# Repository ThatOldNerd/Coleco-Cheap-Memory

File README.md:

# Coleco-Cheap-Memory
This is an inexpensive memory module for the Colecovision Adam

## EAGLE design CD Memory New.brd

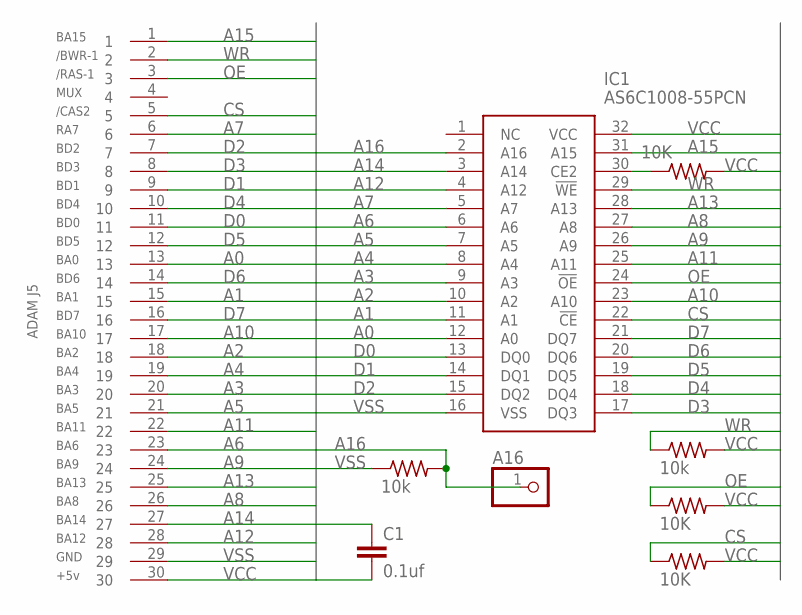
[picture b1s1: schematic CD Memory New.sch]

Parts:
A16: PINHD-1X1; 1X01
C1: 0.1uf; C050-030X075
IC1: AS6C1008-55PCN; DIP254P1524X393-32
R1, R3, R4: 10K; V526-0
R2, R5: 10k; V526-0
U$1: MEM_CARD_NO_OUTLINE; J5CARD_NO_OUTLINE

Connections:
A0: IC1.12 (A0), U$1.13
A1: IC1.11 (A1), U$1.15
A2: IC1.10 (A2), U$1.18
A3: IC1.9 (A3), U$1.20
A4: IC1.8 (A4), U$1.19
A5: IC1.7 (A5), U$1.21
A6: IC1.6 (A6), U$1.23
A7: IC1.5 (A7), U$1.6
A8: IC1.27 (A8), U$1.26
A9: IC1.26 (A9), U$1.24
A10: IC1.23 (A10), U$1.17
A11: IC1.25 (A11), U$1.22
A12: IC1.4 (A12), U$1.28
A13: IC1.28 (A13), U$1.25
A14: IC1.3 (A14), U$1.27
A15: IC1.31 (A15), U$1.1
A16: A16.1, IC1.2 (A16), R5.2
CS: IC1.22 (!CE), R4.1, U$1.5
D0: IC1.13 (DQ0), U$1.11
D1: IC1.14 (DQ1), U$1.9
D2: IC1.15 (DQ2), U$1.7
D3: IC1.17 (DQ3), U$1.8
D4: IC1.18 (DQ4), U$1.10
D5: IC1.19 (DQ5), U$1.12
D6: IC1.20 (DQ6), U$1.14
D7: IC1.21 (DQ7), U$1.16
unnamed: IC1.30 (CE2), R1.1
OE: IC1.24 (!OE), R3.1, U$1.3
VCC: C1.2, IC1.32 (VCC), R1.2, R2.2, R3.2, R4.2, U$1.30
VSS: C1.1, IC1.16 (VSS), R5.1, U$1.29
WR: IC1.29 (!WE), R2.1, U$1.2

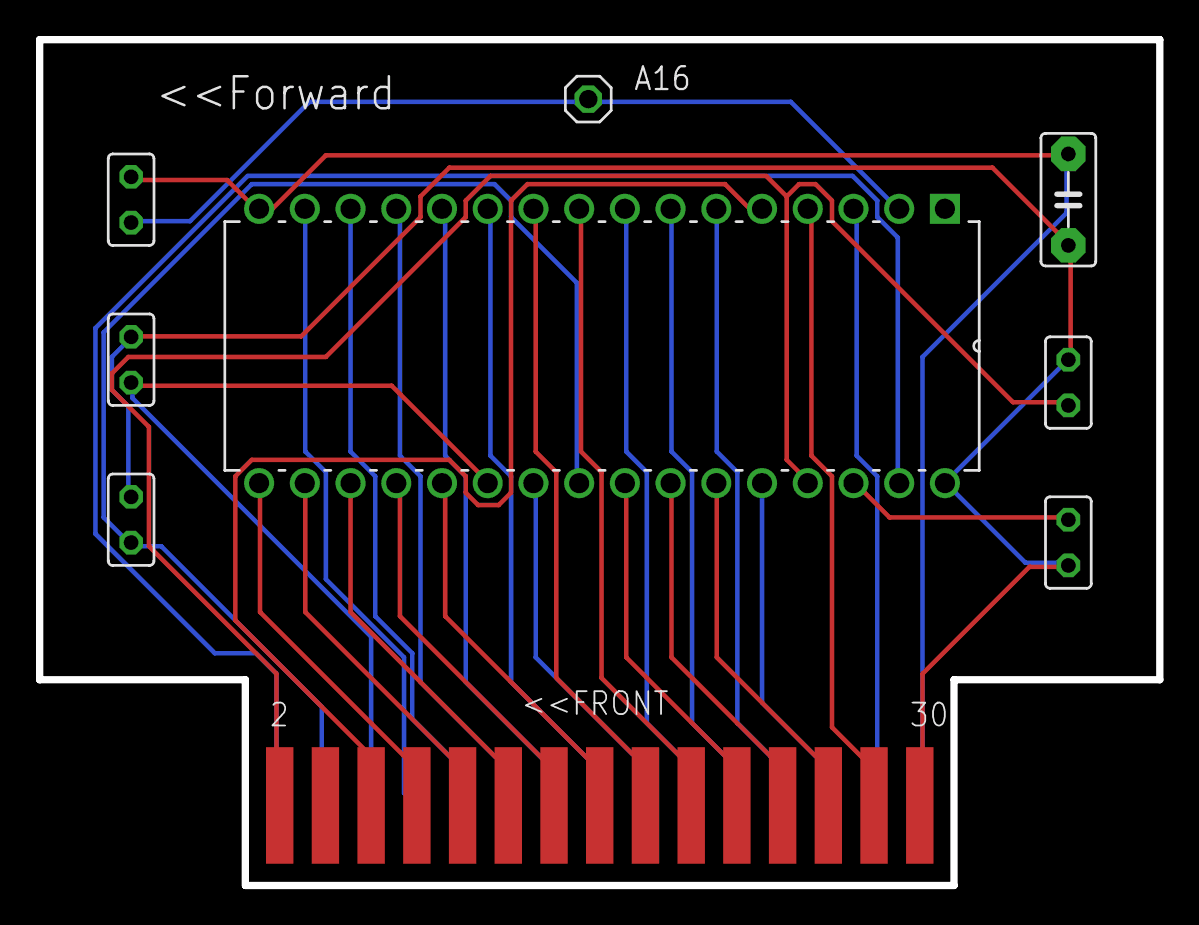
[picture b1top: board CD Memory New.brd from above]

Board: 2 copper layers, 62.2 x 47.0 mm, 9 parts (0 on the bottom side), 31 nets.
